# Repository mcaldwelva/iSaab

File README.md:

# iSaab
This module replaces the factory CD changer on the Saab 9-3 OG and 9-5 OG. All controls behave as the original, with the following exceptions:
* RDM does not change tracks when switching to shuffle mode

* In shuffle mode, the NXT and preset buttons are used to change the display text. NXT will rotate through the tags. Each preset button will select: 1) Track Title, 2) Album Title, 3) Album Artist, 4) Track Artist, 5) Genere, or 6) Year, respectively. Pressing the same preset again will return the display to normal.

* The 9-5 intro scan controls have been repurposed for pause and resume

## Parts

This is based on the [BlueSaab 3.5mm module](http://bluesaab.blogspot.com/2014/03/how-to-build-your-own-35mm-version-of.html) with some modifications to incorporate a sound card and reduce power consumption. The following or similar parts are required:

* [iSaab board](https://oshpark.com/shared_projects/o4QRu2nz)

* [ICs, caps, resistors, etc.](https://www.mouser.com/ProjectManager/ProjectDetail.aspx?AccessID=5A5DA965B5)

* [TE 827229-1 connector](https://www.connectorpeople.com/Connector/TYCO-AMP-TE_CONNECTIVITY/8/827229-1)

* [VS1053 breakout board](https://www.amazon.com/VS1053-VS1053B-Real-Time-Recording-Arduino/dp/B09134QG8Y)

* FTDI cable

* 9-5 only: CD Changer Connector Harness (400129243)

## Build

The BOM components are labeled to match the board. Cut the ribbon cable and strip the even wires (only the bottom row is used) so that they can be solderd in place with the MCU from the underside of the board.

| VS1053 Pin | AVR Pin | Ribbon Pin |
| ----------:|:------- | ---------- |
| 5V         | 20      | 1 |
| GND        | 22      | 2 |
| CARDCS     | 6 (D4)  | 3 |
| MISO       | 18      | 4 |
| MOSI       | 17      | 5 |
| SCK        | 19      | 6 |
| XCS        | 13 (D7) | 7 |
| XRESET     | 15 (D9) | 8 |
| XDCS       | 12 (D6) | 9 |
| DREQ       | 5  (D3) | 10 |

## Software

* Use Arduino 2.2.1 (or higher)

* Apply the [SD library patch](https://raw.githubusercontent.com/mcaldwelva/iSaab/master/data/SD.diff) to fix performance issues:

> patch -p1 -d %LOCALAPPDATA%\Arduino15\libraries < %HOMEPATH%\Documents\Arduino\iSaab\data\SD.diff

* Upload the iSaab code to the module using an FTDI cable

## Usage
* Format an SD card with FAT32. Third-party tools are needed to format SD cards larger than 32GB (e.g.
http://www.ridgecrop.demon.co.uk/index.htm?fat32format.htm)

* Place FLAC, Ogg Vorbis, MP3, AAC, or WMA music files into sub-directories, up-to three levels deep

* Files are played in filesystem order, which may not be as they appear in your OS. Third-party tools can be used to sort the filesystem to play in the desired order (e.g. http://www.anerty.net/software/file/DriveSort.php)

* Place [patch053.bin](https://raw.githubusercontent.com/mcaldwelva/iSaab/master/data/patch053.bin) in the root folder to enable FLAC playback.

* Create presets.txt in the root, containing up to 6 comma separated numbers. Each number represents the play-order of the file on the file system.

* Connect the module to the CD changer port in the trunk:

## Troubleshooting
* The disc and track numbers are changing on the display but nothing is playing. This is expected behavior when seeking tracks. You may see this when the CD changer turns on, when selecting a preset, or between tracks in shuffle mode.

* If play doesn't start when the CD changer is selected, ensure the SD card is fully inserted. If the module is still unrespsonive, it may be necessary to disconnect and reconnect it for a hard boot.

* Only connect or disconnnect the module while the car is off and key removed from the ingition.

* When the module is shutdown, only the LED on the daughter card will remain lit to indicate power. The module draws ~13mA in this state.

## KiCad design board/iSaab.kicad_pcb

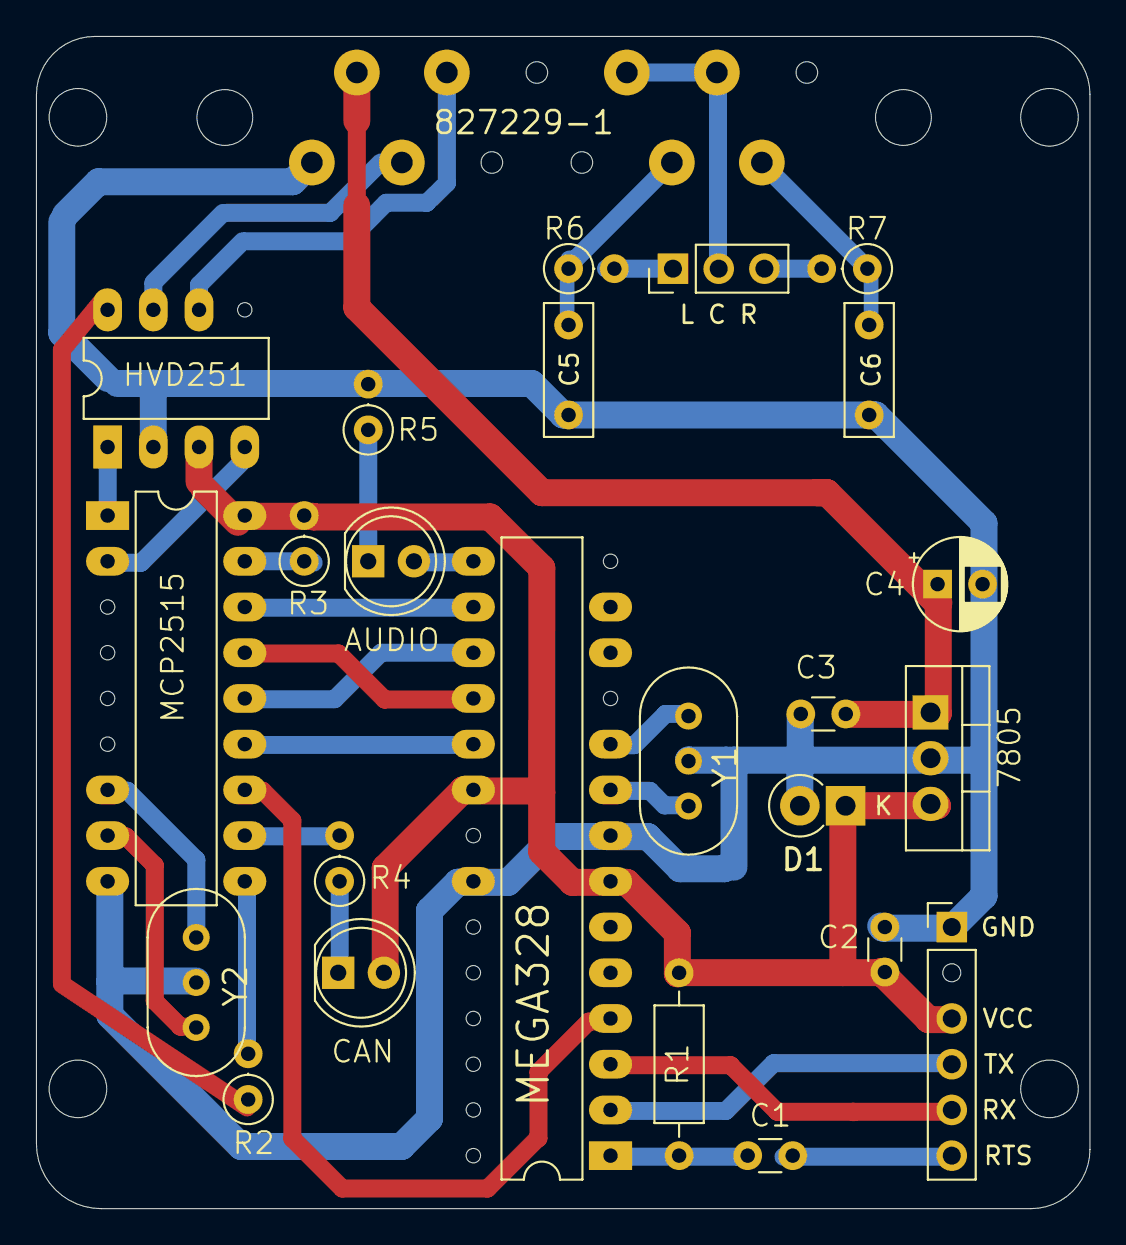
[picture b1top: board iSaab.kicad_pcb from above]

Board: 2 copper layers, 58.5 x 65.1 mm, 29 parts (0 on the bottom side), 32 nets.

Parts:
@HOLE0, @HOLE1, @HOLE2, @HOLE3: (no value)
AUDIO: 5V; LED_D5.0mm
Audio In: L C R; PinHeader_1x03_P2.54mm_Vertical
C1, C2: 0.1uF; C_Disc_D3.0mm_W1.6mm_P2.50mm
C3: 470nF; C_Disc_D3.0mm_W1.6mm_P2.50mm
C4: 1uF; CP_Radial_D5.0mm_P2.50mm
C5, C6: 4.7nF; C_Rect_L7.2mm_W2.5mm_P5.00mm_FKS2_FKP2_MKS2_MKP2
CAN: 5V; LED_D5.0mm
D1: 1N4007-01; D_DO-41_SOD81_P2.54mm_Vertical_KathodeUp
IC1: MCP2515; DIP-18_W7.62mm_LongPads
IC2: HVD251; DIP-8_W7.62mm_LongPads
IC3: MEGA328; DIP-28_W7.62mm_LongPads
IC4: 7805; TO-220-3_Vertical
JP1: FTDI; PinHeader_1x06_P2.54mm_Vertical
R1: 10K; R_Axial_DIN0207_L6.3mm_D2.5mm_P10.16mm_Horizontal
R2, R3: 10K; R_Axial_DIN0207_L6.3mm_D2.5mm_P2.54mm_Vertical
R4, R5, R6, R7: 1K; R_Axial_DIN0207_L6.3mm_D2.5mm_P2.54mm_Vertical
U$5: 827229-1
Y1, Y2: 16MHz; Resonator-3Pin_W10.0mm_H5.0mm

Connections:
+5V: C2.1, CAN.2, D1.1, IC1.18, IC2.3, IC3.7, IC3.20, IC4.3, JP1.3, R1.1, R3.2
+12: C3.1, C4.1, IC4.1, U$5.6
CANH: IC2.7, U$5.11
CANL: IC2.6, U$5.5
CS: IC1.16, IC3.16
GBUF: Audio In.2, U$5.2, U$5.3
GND: C2.2, C3.2, C4.2, C5.1, C6.1, D1.2, IC1.9, IC2.2, IC3.8, IC3.22, IC4.2, JP1.1, R5.2, U$5.12, Y1.2, Y2.2
INT: IC1.12, IC3.4
LOUT: C5.2, R6.1, U$5.8
MISO: IC1.15, IC3.18
MOSI: IC1.14, IC3.17
unnamed: CAN.1, R4.1
unnamed: AUDIO.1, R5.1
unnamed: Audio In.1, R6.2
unnamed: Audio In.3, R7.2
unnamed: IC1.17, R3.1
OSC1: IC1.8, Y2.3
OSC2: IC1.7, Y2.1
RESET: C1.1, IC3.1, R1.2
ROUT: C6.2, R7.1, U$5.7
RTS: C1.2, JP1.6
RX: IC3.3, JP1.5
RX0BF: IC1.11, R4.2
RX1BF: IC1.10, R2.2
RXCAN: IC1.2, IC2.4
SCK: IC1.13, IC3.19
STDBY: IC2.8, R2.1
TOSC1: IC3.9, Y1.1
TOSC2: IC3.10, Y1.3
TX: IC3.2, JP1.4
TXCAN: IC1.1, IC2.1
XRESET: AUDIO.2, IC3.15

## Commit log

2015-11-04 new file: CAN.cpp new file: CAN.h new file: Player.cpp new file: Player.h new file: README.md new file: VS1053.cpp new file: VS1053.h new file: data/back.jpg new file: data/front.jpg new file: data/i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
2015-11-05 modified: Player.cpp modified: iSaab.ino
2015-11-07 modified: tags.cpp
2015-11-12 modified: Player.cpp modified: iSaab.ino deleted: tags.cpp deleted: tags.h
2015-11-20 modified: VS1053.cpp modified: iSaab.h modified: iSaab.ino
2015-11-22 modified: Player.cpp modified: Player.h modified: VS1053.cpp modified: VS1053.h
2015-11-23 modified: Player.cpp
2015-12-02 modified: Player.cpp modified: VS1053.h modified: iSaab.h modified: iSaab.ino
2015-12-07 modified: Player.cpp modified: Player.h modified: VS1053.cpp modified: VS1053.h modified: iSaab.h modified: iSaab.ino
2015-12-07 modified: VS1053.cpp
2016-01-07 modified: Player.cpp modified: Player.h modified: VS1053.h
2016-01-08 modified: Player.cpp modified: VS1053.h
2016-01-20 modified: README.md
2016-01-20 modified: iSaab.ino
2016-02-01 modified: Player.cpp modified: VS1053.cpp modified: VS1053.h MediaFile.cpp MediaFile.h
2016-02-01 new file: MediaFile.cpp new file: MediaFile.h modified: Player.cpp
2016-02-01 modified: MediaFile.cpp
2016-02-16 Overhauled to use SDLib's disk buffer
2016-02-22 Testing display code
2016-02-23 cleaned up text interface
2016-02-24 enable/disable low priority CAN interrutps
2016-02-25 using row 0
2016-02-25 modified: MediaFile.cpp modified: Player.cpp modified: Player.h modified: iSaab.ino
2016-02-26 type cleanup
2016-02-26 modified: Player.cpp modified: Player.h modified: iSaab.ino
2016-02-26 modified: Player.h
2016-02-28 added Ogg support
2016-02-29 added Genre and AlbumArtist tags
2016-03-02 modified: CAN.cpp modified: MediaFile.cpp testing OSM again
2016-03-04 renamed: MediaFile.cpp -> AudioFile.cpp
2016-03-08 tag parser clean-up
2016-03-08 fixed message transmission order
2016-03-10 max SDI speed
2016-03-11 turn off display during rapid play
2016-03-11 temporary display fix
2016-03-14 CAN library improvements
2016-03-14 modified: CAN.cpp
2016-03-15 modified: AudioFile.cpp
2016-03-17 simplified CAN public interface
2016-03-23 more CAN interface clean-up
2016-03-26 speed up file search
2016-03-29 send full presence sequence
2016-03-31 don't hog SPI
2016-03-31 clean-up
2016-04-02 allow changing SD card, full-speed SPI, extended ASCII filenames
2016-04-07 a little more random
2016-04-14 renamed some things
2016-04-20 separate MCU sleep from CAN sleep
2016-05-25 fixes potential issues on shutdown and changing tracks
2016-06-02 revert sciRead/Write
2016-06-15 better fix for delayed shutdown
2016-07-26 openNextTrack clean-up
2016-07-27 CDC needs to be active to receive shutdown message
2016-08-01 openNextTrack optimizations
2016-08-08 fixed TCON/TCO
2016-08-08 relabeled 6a1/6a2 messages
2016-08-10 fix folder count
2016-08-21 improved track skipping in-folder
2016-08-21 no real benefit to state 5
2016-08-24 VS1053b patch v2.40
2016-08-30 always use the same power status
2016-10-12 fixed occasional dropped messages
2016-11-29 fix hang if file closed while reading FLAC header
2017-01-13 better handling of file headers
2017-01-14 revised OGG handling
2017-01-23 don't show old text
2017-02-01 support WMA tags
2017-02-01 WMA const cleanup
2017-02-11 added support for iTunes tags
2017-02-11 iTunes a little more efficient
2017-02-15 swap TPE1 & TPE2
2017-02-28 trivia
2017-03-07 updated pic
2017-03-08 no previous track in shuffle mode
2017-03-10 use 9-5 scan commands for pause/resume
2017-03-17 added comments
2017-03-29 get endfillbyte before cancel
2017-10-03 always use 0 to flush buffer
2017-10-04 check HDAT1 instead of CANCEL
2017-10-05 do multiple checks to ensure buffer is cleared
2017-10-06 2 cancels is more reliable/less noise
2017-10-11 use RX1BF to manage transceiver
2017-10-29 modified to use transceiver standby
2017-10-31 wait a little longer for standby
2017-11-15 handle file close while reading header
2017-12-07 added some debugging
2017-12-07 reset overflow after checking
2017-12-08 tweak debug output
2017-12-08 keep debug displayed
2018-01-02 use ListenOnly w/ transceiver standby
2018-01-05 skip hidden or system files and directories
2018-01-24 VS1053b patch v2.50
2018-04-06 removed line drivers
2018-04-11 wait for start-up before changing reference
2018-04-12 added output resistors
2018-05-12 VS1053b patch v2.60
2018-05-15 allow hidden/system files to be opened explicitly
2018-05-19 minimize data interrupts
2018-05-25 CANCEL until HDAT1 clears
2018-06-01 use SD buffer for reading tags
2018-06-05 flush buffer before cancel
2018-07-06 start with ListenOnly
2018-08-21 MP4 tweaks
2018-08-23 not supporting ancient Arduino libraries
2018-08-28 safe update of current track number
2018-09-07 reuse macros
2018-10-02 tweaked readTag
2018-12-17 gcc 5.4.0 causing problems
2018-12-19 wait for HDAT to clear after cancel
2018-12-19 wait longer for standby
2018-12-24 use SDLib 1.2.3
2019-01-08 move HDAT delay as late as possible
2019-01-10 merged DSD changes
2019-01-17 merged some changes
2019-01-22 merged random
2019-02-06 more debug info
2019-02-07 tweak random
2019-02-11 comment clean-up
2019-02-11 line-ending clean-up
2019-02-12 fixed byterate for DSD
2019-02-22 a byte too far
2019-03-02 improved startup/shutdown
2019-03-06 SD isn't thread-safe
2019-03-06 make SD type_ volatile
2019-03-07 startup based on selected device
2019-10-03 use SD.end()
2019-11-01 fix ogg seg count
2019-11-29 single CAN instance
2019-11-30 VS1053b patch v2.70
2019-12-04 add board
2019-12-04 refactor getStatus()
2019-12-04 tweak trackTime()
2019-12-08 refactor display
2019-12-09 refactor display
    refactor display
2019-12-19 mind the heap
2020-01-14 merged serial interface
2020-01-14 reintroduce display reset
2020-01-21 net clean-up
2020-01-23 BOM update
2020-01-30 static CDC instance
2020-02-07 show resonator labels
2020-02-11 added troubleshooting
2020-02-20 Updated to 1.8.12
2020-03-18 new board
2020-04-02 updated images
2020-04-14 header clean-up
2020-04-14 handle some EOF situations
2021-02-15 VS1053b patch v2.90
2021-03-17 fix for empty folders
2021-06-11 tweak plugin loader
2021-07-15 fix skipped track when paused
2022-09-14 improve filesystem performance
2024-01-24 fix file jump
